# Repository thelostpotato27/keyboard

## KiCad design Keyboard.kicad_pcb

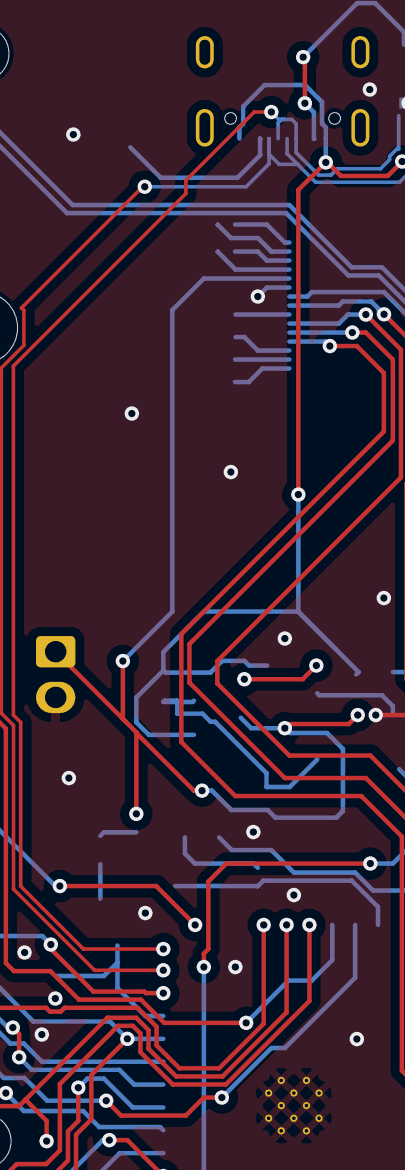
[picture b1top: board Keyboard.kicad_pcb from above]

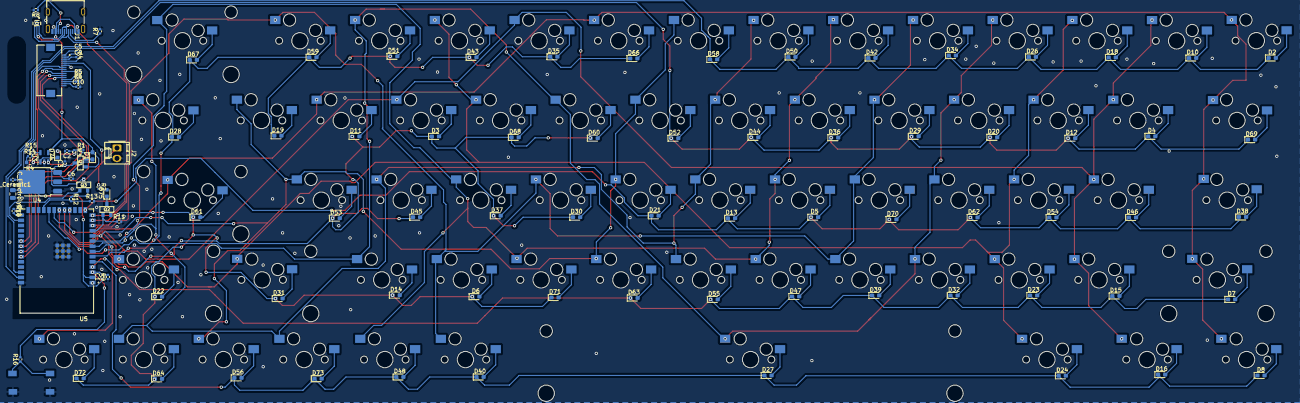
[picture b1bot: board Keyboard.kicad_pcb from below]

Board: 2 copper layers, 168 parts (104 on the bottom side), 101 nets.

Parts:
C1, C5, C9: 1uF; C_0402_1005Metric
C2, C3: 4.7uF; C_0402_1005Metric
C4, C6, C10: 10uF; C_0402_1005Metric
C_Ceramic1: .1uF; C_0402_1005Metric
C_Electrolytic1: 22uF; C_0805_2012Metric
D1, D2, D3, D4, D5, D6, D7, D8, D10, D11, D12, D13, D14, D15, D16, D18, D19, D20, D21, D22, D23, D24, D26, D27, D28, D29, D30, D31, D32, D34, D35, D36, D37, D38, D39, D40, D42, D43, D44, D45, D46, D47, D48, D50, D51, D52, D53, D54, D55, D56, D58, D59, D60, D61, D62, D63, D64, D66, D67, D68, D69, D70, D71, D72, D73: D; D_0603_1608Metric_Pad1.05x0.95mm_HandSolder
D74, D75: LED; LED_0603_1608Metric
J1: USB_C_Receptacle; USB_C_Receptacle_G-Switch_GT-USB-7010ASV
J2: Conn_02x01; Molex_KK-254_AE-6410-02A_1x02_P2.54mm_Vertical
J4: FFC2B35-16-G_REVA2; GCT_FFC2B35-16-G_REVA2
K1, K2, K3, K4, K5, K9, K10, K11, K12, K13, K14, K17, K18, K19, K20, K21, K22, K25, K27, K28, K30, K33, K34, K35, K36, K38, K39, K41, K42, K43, K44, K45, K46, K47, K49, K50, K51, K52, K53, K54, K55, K57, K58, K59, K61, K62, K63, K65, K67, K69, K70, K71, K72: KEYSW; Cherry-MX_PCB-Mounted_LTST-A683CEGBW_Kailh_Socket
K6, K29, K66: KEYSW; SW_Cherry_MX_2.00u_PCB
K7, K15, K23: KEYSW; SW_Cherry_MX_1.25u_PCB
K26, K68: KEYSW; SW_Cherry_MX_1.50u_PCB
K31: KEYSW; SW_Cherry_MX_6.25u_PCB
K37: KEYSW; SW_Cherry_MX_1.75u_PCB
K60: KEYSW; SW_Cherry_MX_2.25u_PCB
Q1: PMOS; MOS_FET_SOT23-3_HSOL
Q2, Q3: NMOS; MOS_FET_SOT23-3_HSOL
R1, R11: 20k; R_0402_1005Metric
R2, R3: 470; R_0402_1005Metric
R4: 500; R_0603_1608Metric
R5: 680k; R_0402_1005Metric
R6: 5.1kOhm; R_0402_1005Metric
R7, R8, R16: 5.1k ohm; R_0402_1005Metric
R9: 10k; R_0402_1005Metric
R10: 2M; R_0402_1005Metric
R12: 120; R_0402_1005Metric
R13, R14, R15: 1k; R_0402_1005Metric
SW1: SW_MEC_5G; SW_MEC_5GSH9
U1: VBUS54CV-HSF-G4-08; SMT_CV-HSF-G4-08_VIS
U3: MCP73831-2-OT; SOT-23-5
U4: LM1117DT-3.3; TO-252-3_TabPin2
U5: ESP32-S3-WROOM-1-N16R2; XCVR_ESP32-S3-WROOM-1-N16R2

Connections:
Col 1: K1.1, K10.1, K65.1, U5.18 (IO10)
Col 2: K2.1, K3.1, K9.1, K14.1, K21.1, K34.1, K45.1, U5.19 (IO11)
Col 3: K11.1, K17.1, K22.1, K42.1, K53.1, K67.1, U5.20 (IO12)
Col 4: K13.1, K19.1, K25.1, K30.1, K50.1, K59.1, K61.1, U5.22 (IO14)
Col 5: K5.1, K27.1, K28.1, K33.1, K38.1, K39.1, K58.1, K69.1, U5.21 (IO13)
Col 6: K4.1, K35.1, K36.1, K41.1, K46.1, K47.1, K70.1, U5.8 (IO15)
Col 7: K12.1, K43.1, K44.1, K49.1, K54.1, K63.1, K72.1, U5.9 (IO16)
Col 8: K18.1, K20.1, K51.1, K52.1, K55.1, K57.1, K62.1, K71.1, U5.10 (IO17)
D+: J1.A6 (D+), J1.B6 (D+), U1.6, U5.14 (IO20)
D-: J1.A7 (D-), J1.B7 (D-), U1.4, U5.13 (IO19)
EN In: C1.1, C_Ceramic1.1, C_Electrolytic1.1, J4.7, U4.2 (VO), U5.2 (3V3)
GND: C2.2, C3.2, C4.2, C6.2, C10.2, C_Ceramic1.2, C_Electrolytic1.2, J1.A1 (GND), J1.A12 (GND), J1.B1 (GND), J1.B12 (GND), J2.2, J4.6, J4.16, Q2.S, R1.2, R4.1, R5.2, R6.1, R7.2, R8.2, R9.1, R10.1, R11.2, R13.2, SW1.1 (A), SW1.2 (A), U1.2, U3.2 (V_{SS}), U4.1 (GND), U5.1 (GND), U5.40 (GND), U5.41_1 (GND), U5.41_2 (GND), U5.41_3 (GND), U5.41_4 (GND), U5.41_5 (GND), U5.41_6 (GND), U5.41_7 (GND), U5.41_8 (GND), U5.41_9 (GND), U5.41_10, U5.41_11, U5.41_12, U5.41_13, U5.41_14, U5.41_15, U5.41_16, U5.41_17, U5.41_18, U5.41_19, U5.41_20, U5.41_21
LED Out: R11.1, U5.11 (IO18)
MOSI: J4.12, U5.35 (IO42)
unnamed: C4.1, J4.14
unnamed: C5.1, J4.1
unnamed: C5.2, J4.2
unnamed: C9.1, J4.3
unnamed: C9.2, J4.4
unnamed: C10.1, J4.15
unnamed: C6.1, D1.1 (K), U4.3 (VI)
unnamed: D2.2 (A), K1.2
unnamed: D3.2 (A), K2.2
unnamed: D4.2 (A), K3.2
unnamed: D5.2 (A), K4.2
unnamed: D6.2 (A), K5.2
unnamed: D10.2 (A), K9.2
unnamed: D11.2 (A), K10.2
unnamed: D12.2 (A), K11.2
unnamed: D13.2 (A), K12.2
unnamed: D14.2 (A), K13.2
unnamed: D15.2 (A), K14.2
unnamed: D18.2 (A), K17.2
unnamed: D19.2 (A), K18.2
unnamed: D20.2 (A), K19.2
unnamed: D21.2 (A), K20.2
unnamed: D22.2 (A), K21.2
unnamed: D23.2 (A), K22.2
unnamed: D26.2 (A), K25.2
unnamed: D29.2 (A), K27.2
unnamed: D30.2 (A), K28.2
unnamed: D32.2 (A), K30.2
unnamed: D34.2 (A), K33.2
unnamed: D35.2 (A), K34.2
unnamed: D36.2 (A), K35.2
unnamed: D37.2 (A), K36.2
unnamed: D39.2 (A), K38.2
unnamed: D40.2 (A), K39.2
unnamed: D42.2 (A), K41.2
unnamed: D43.2 (A), K42.2
unnamed: D44.2 (A), K43.2
unnamed: D45.2 (A), K44.2
unnamed: D46.2 (A), K45.2
unnamed: D47.2 (A), K46.2
unnamed: D48.2 (A), K47.2
unnamed: D50.2 (A), K49.2
unnamed: D51.2 (A), K50.2
unnamed: D52.2 (A), K51.2
unnamed: D53.2 (A), K52.2
unnamed: D54.2 (A), K53.2
unnamed: D55.2 (A), K54.2
unnamed: D56.2 (A), K55.2
unnamed: D58.2 (A), K57.2
unnamed: D59.2 (A), K58.2
unnamed: D60.2 (A), K59.2
unnamed: D62.2 (A), K61.2
unnamed: D63.2 (A), K62.2
unnamed: D64.2 (A), K63.2
unnamed: D66.2 (A), K65.2
unnamed: D68.2 (A), K67.2
unnamed: D70.2 (A), K69.2
unnamed: D71.2 (A), K70.2
unnamed: D72.2 (A), K71.2
unnamed: D73.2 (A), K72.2
unnamed: D74.2 (A), R3.2
unnamed: D75.2 (A), R2.2
unnamed: J1.A5 (CC1), R7.1
unnamed: J1.B5 (CC2), R8.1
unnamed: J4.13, R5.1
unnamed: R4.2, R14.1
unnamed: R14.2, R15.1
unnamed: R16.1, SW1.3 (B), SW1.4 (B)
unnamed: R15.2, U3.5 (PROG)
unnamed: C1.2, R9.2, R16.2, U5.3 (EN)
unnamed: R10.2, U5.27 (IO0)
OLED_CS: J4.8, U5.32 (IO39)
OLED_DC: J4.10, U5.33 (IO40)
OLED_RST: J4.9, R6.2
Row 1: D2.1 (K), D10.1 (K), D18.1 (K), D26.1 (K), D34.1 (K), D42.1 (K), D50.1 (K), D58.1 (K), U5.39 (IO1)
Row 2: D4.1 (K), D12.1 (K), D20.1 (K), D29.1 (K), D36.1 (K), D44.1 (K), D52.1 (K), D69.1 (K), U5.38 (IO2)
Row 3: D5.1 (K), D13.1 (K), D21.1 (K), D38.1 (K), D46.1 (K), D54.1 (K), D62.1 (K), D70.1 (K), U5.15 (IO3)
Row 4: D7.1 (K), D15.1 (K), D23.1 (K), D32.1 (K), D39.1 (K), D47.1 (K), D55.1 (K), D63.1 (K), U5.4 (IO4)
Row 5: D8.1 (K), D16.1 (K), D24.1 (K), D27.1 (K), D40.1 (K), D48.1 (K), D56.1 (K), D73.1 (K), U5.5 (IO5)
Row 6: D19.1 (K), D28.1 (K), D35.1 (K), D43.1 (K), D51.1 (K), D59.1 (K), D66.1 (K), D67.1 (K), U5.6 (IO6)
Row 7: D3.1 (K), D11.1 (K), D30.1 (K), D37.1 (K), D45.1 (K), D53.1 (K), D60.1 (K), D68.1 (K), U5.7 (IO7)
Row 8: D6.1 (K), D14.1 (K), D22.1 (K), D31.1 (K), D61.1 (K), D64.1 (K), D71.1 (K), D72.1 (K), U5.12 (IO8)
SCK: J4.11, U5.34 (IO41)
Stat in: D74.1 (K), U3.1 (STAT)
VBAT: C3.1, J4.5, R2.1, U3.3 (V_{BAT})
VBUS: C2.1, D1.2 (A), J1.A4 (VBUS), J1.A9 (VBUS), J1.B4 (VBUS), J1.B9 (VBUS), R1.1, R3.1, U1.5, U3.4 (V_{DD})
Voltage Check: R12.2, R13.1, U5.23 (IO21)

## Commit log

2023-11-19 stored keyboard files here to work on laptop and desktop
2023-11-20 some edits
2023-11-21 updated keyboard to have working (theoretically) battery overcharge protector
2023-11-21 setting up desktop branch
2023-11-22 finished keyboard matrix, worked on LED backlight
2023-11-24 bare bones of the keyboard complete
2023-12-01 keyboard progress
2023-12-01 started working with another microcontroller
2023-12-03 added mosfets for clearly marking what is powering board
2023-12-05 started on pcb
2023-12-07 finished logic layout, need to connect pins to keys
2023-12-08 made further progress on the keyboard pcb
2023-12-08 basically finished wiring, now just need to add reset button and video wire hole
2023-12-10 finished pcb
2023-12-10 edited some minor mistakes, it works properly now
